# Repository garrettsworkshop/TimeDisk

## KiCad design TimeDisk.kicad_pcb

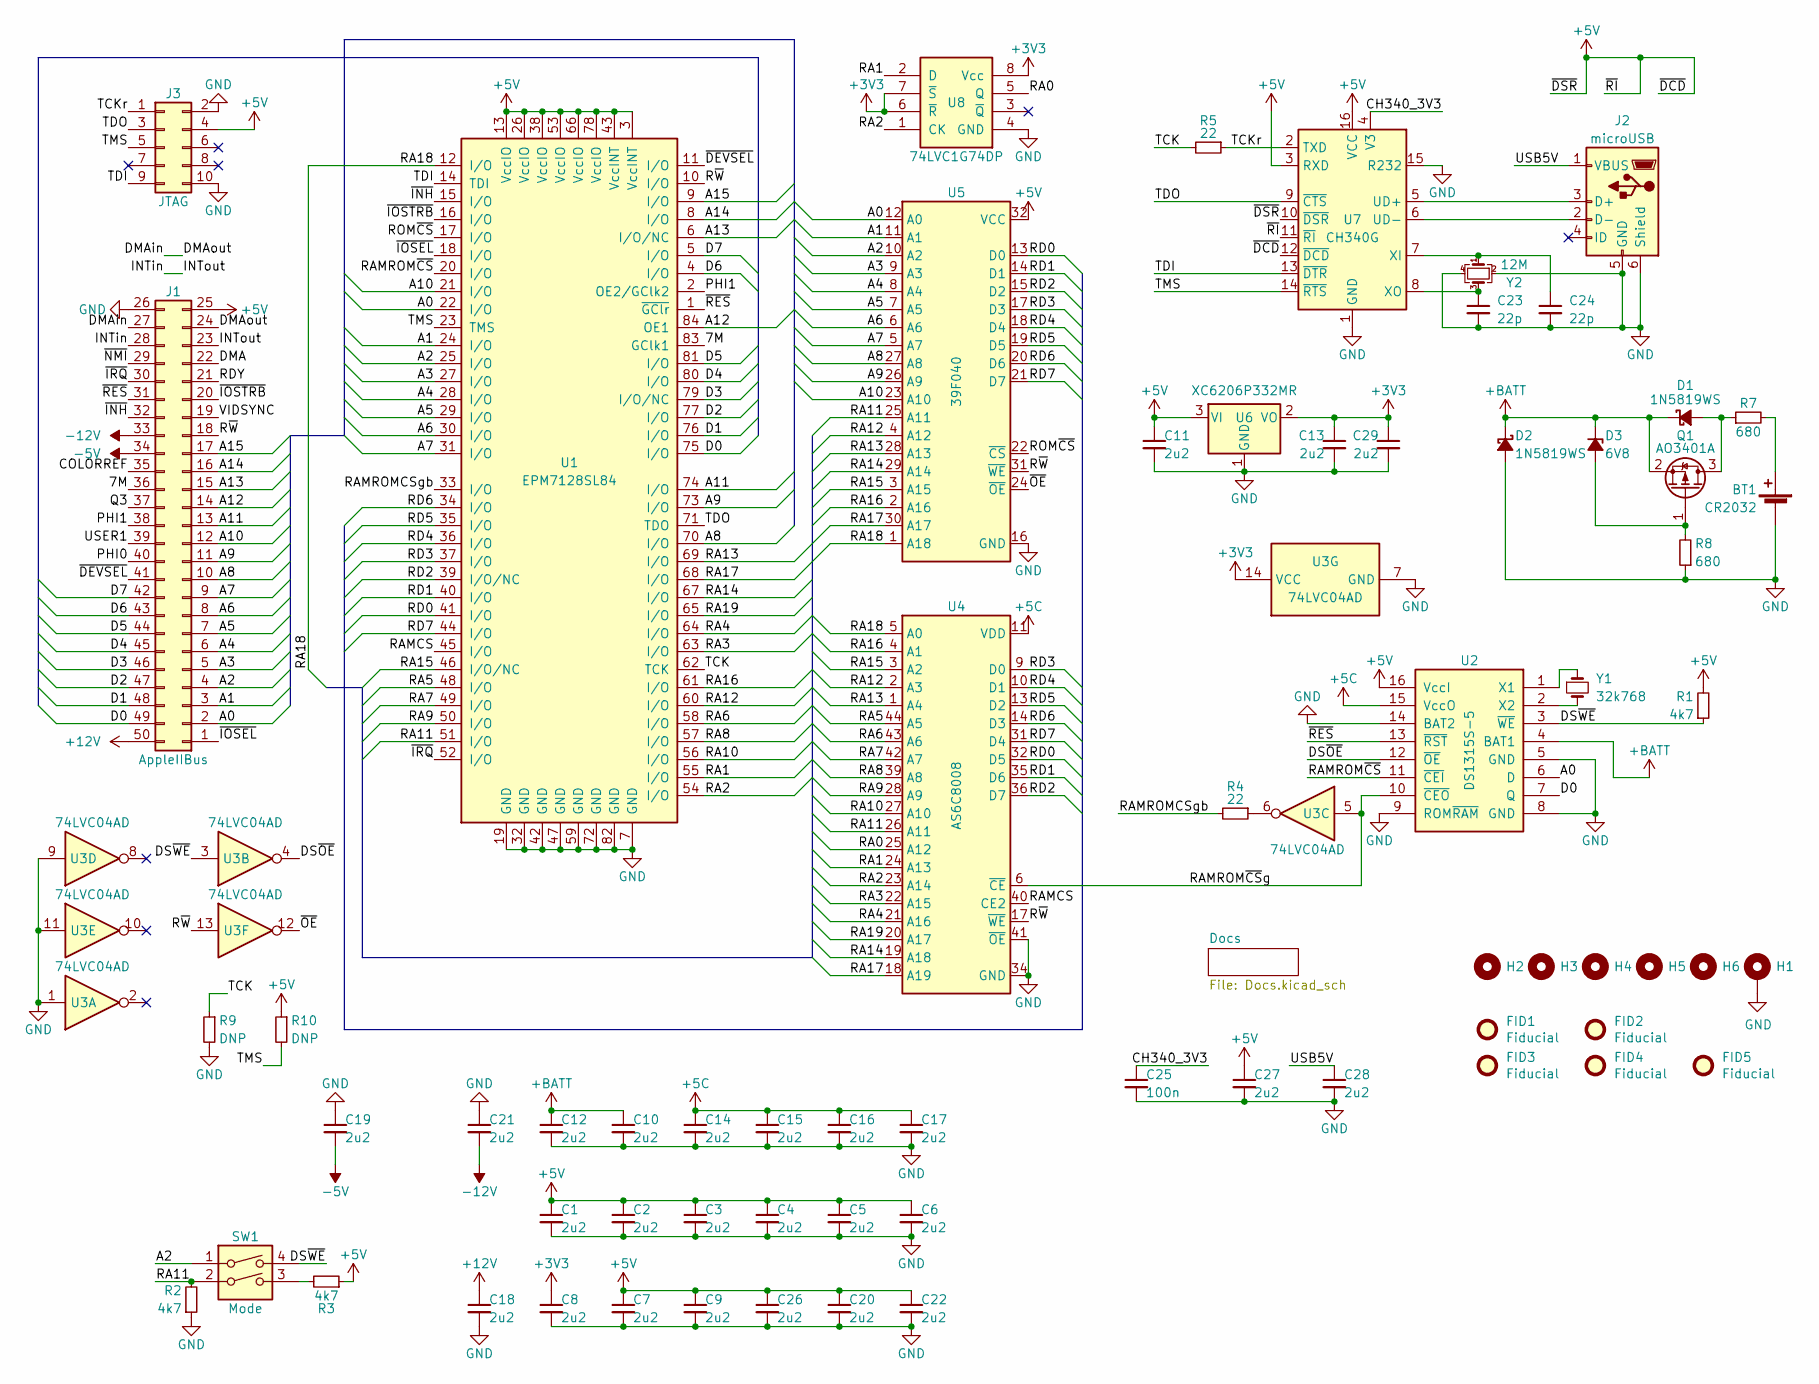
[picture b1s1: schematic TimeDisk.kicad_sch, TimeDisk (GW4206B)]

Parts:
BT1: CR2032; Keystone_3034_2032; LCSC Part C964833
C1, C2, C3, C4, C5, C6, C7, C8, C9, C10, C11, C12, C13, C14, C15, C16, C17, C18, C19, C20, C21, C22, C26, C27, C28, C29: 2u2; C_0805; LCSC Part C87994
C23, C24: 22p; C_0603; LCSC Part C1653
C25: 100n; C_0603; LCSC Part C28233
D1, D2: 1N5819WS; D_SOD-123; LCSC Part C191023
D3: 6V8; D_SOD-323; LCSC Part C118604
FID1, FID2, FID3, FID4, FID5: Fiducial
H1: PasteHole_1.1mm_PTH
H2, H3, H4, H5, H6: PasteHole_1.152mm_NPTH
J1: AppleIIBus; AppleIIBus_Edge
J2: microUSB; USB_Micro-B_Amphenol_10118192-0001; LCSC Part C132564
J3: JTAG; Header_2x5_Unshrouded_P1.27mm
Q1: AO3401A; SOT-23; LCSC Part C15127
R1, R2, R3: 4k7; R_0805; LCSC Part C17673
R4, R5: 22; R_0805; LCSC Part C17561
R7, R8: 680; R_0805; LCSC Part C17798
R9, R10: DNP; R_0805
SW1: Mode; SW_DIP_SPSTx02_Slide_DSHP02TS_P1.27mm
U1: EPM7128SL84; PLCC-84
U2: DS1315S-5; SOIC-16_7.5mm
U3: 74LVC04AD; SOIC-14_3.9mm; LCSC Part C190764
U4: AS6C8008; TSOP-II-44_400mil_P0.8mm; LCSC Part C1349342
U5: 39F040; PLCC-32_SMDSocket; LCSC Part C645936
U6: XC6206P332MR; SOT-23; LCSC Part C5446
U7: CH340G; SOIC-16_3.9mm; LCSC Part C14267
U8: 74LVC1G74DP; NXP_TSSOP-8_3x3mm_P0.65mm; LCSC Part C458768
Y1: 32k768; Crystal_C26-LF_D2.1mm_L6.5mm_Horizontal
Y2: 12M; Crystal_SMD_3225-4Pin_3.2x2.5mm; LCSC Part C9002

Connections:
+3V3: C8.1, C13.1, C29.1, U3.14 (VCC), U6.2 (VO), U8.6 (~R), U8.7 (~S), U8.8 (Vcc)
+5C: C14.1, C15.1, C16.1, C17.1, U2.15 (VccO), U4.11 (VDD), U4.33 (VDD)
+5V: C1.1, C2.1, C3.1, C4.1, C5.1, C6.1, C7.1, C9.1, C11.1, C20.1, C22.1, C26.1, C27.1, J1.25, J3.4, R1.2, R3.1, R10.1, U1.3 (VccINT), U1.13 (VccIO), U1.26 (VccIO), U1.38 (VccIO), U1.43 (VccINT), U1.53 (VccIO), U1.66 (VccIO), U1.78 (VccIO), U2.16 (VccI), U5.32 (VCC), U6.3 (VI), U7.3 (RXD), U7.10 (~DSR), U7.11 (~RI), U7.12 (~DCD), U7.16 (VCC)
+12V: C18.1, J1.50
+BATT: C10.1, C12.1, D1.1 (K), D2.1 (K), D3.1 (K), Q1.2 (S), U2.4 (BAT1)
-5V: C19.2, J1.34
-12V: C21.2, J1.33
/7M: J1.36, U1.83 (GClk1)
/A0: J1.2, U1.22 (I/O), U2.6 (D), U5.12 (A0)
/A1: J1.3, U1.24 (I/O), U5.11 (A1)
/A2: J1.4, SW1.1, U1.25 (I/O), U5.10 (A2)
/A3: J1.5, U1.27 (I/O), U5.9 (A3)
/A4: J1.6, U1.28 (I/O), U5.8 (A4)
/A5: J1.7, U1.29 (I/O), U5.7 (A5)
/A6: J1.8, U1.30 (I/O), U5.6 (A6)
/A7: J1.9, U1.31 (I/O), U5.5 (A7)
/A8: J1.10, U1.70 (I/O), U5.27 (A8)
/A9: J1.11, U1.73 (I/O), U5.26 (A9)
/A10: J1.12, U1.21 (I/O), U5.23 (A10)
/A11: J1.13, U1.74 (I/O)
/A12: J1.14, U1.84 (OE1)
/A13: J1.15, U1.6 (I/O/NC)
/A14: J1.16, U1.8 (I/O)
/A15: J1.17, U1.9 (I/O)
/CH340_3V3: C25.1, U7.4 (V3)
/COLORREF: J1.35
/D0: J1.49, U1.75 (I/O), U2.7 (Q)
/D1: J1.48, U1.76 (I/O)
/D2: J1.47, U1.77 (I/O)
/D3: J1.46, U1.79 (I/O/NC)
/D4: J1.45, U1.80 (I/O)
/D5: J1.44, U1.81 (I/O)
/D6: J1.43, U1.4 (I/O)
/D7: J1.42, U1.5 (I/O)
/DMA: J1.22
/DMAin: J1.24, J1.27
/DS~OE: U2.12 (~OE), U3.4
/DS~WE: R1.1, SW1.4, U2.3 (~WE), U3.3
/INTin: J1.23, J1.28
/PHI0: J1.40
/PHI1: J1.38, U1.2 (OE2/GClk2)
/Q3: J1.37
/RA0: U4.25 (A12), U8.5 (Q)
/RA1: U1.55 (I/O), U4.24 (A13), U8.2 (D)
/RA2: U1.54 (I/O), U4.23 (A14), U8.1 (CK)
/RA3: U1.63 (I/O), U4.22 (A15)
/RA4: U1.64 (I/O), U4.21 (A16)
/RA5: U1.48 (I/O), U4.44 (A5)
/RA6: U1.58 (I/O), U4.43 (A6)
/RA7: U1.49 (I/O), U4.42 (A7)
/RA8: U1.57 (I/O), U4.39 (A8)
/RA9: U1.50 (I/O), U4.28 (A9)
/RA10: U1.56 (I/O), U4.27 (A10)
/RA11: R2.2, SW1.2, U1.51 (I/O), U4.26 (A11), U5.25 (A11)
/RA12: U1.60 (I/O), U4.2 (A3), U5.4 (A12)
/RA13: U1.69 (I/O), U4.1 (A4), U5.28 (A13)
/RA14: U1.67 (I/O), U4.19 (A18), U5.29 (A14)
/RA15: U1.46 (I/O/NC), U4.3 (A2), U5.3 (A15)
/RA16: U1.61 (I/O), U4.4 (A1), U5.2 (A16)
/RA17: U1.68 (I/O), U4.18 (A19), U5.30 (A17)
/RA18: U1.12 (I/O), U4.5 (A0), U5.1 (A18)
/RA19: U1.65 (I/O), U4.20 (A17)
/RAMCS: U1.45 (I/O), U4.40 (CE2)
/RAMROMCSgb: R4.2, U1.33 (I/O)
/RAMROM~CS: U1.20 (I/O), U2.11 (~CEI)
/RAMROM~CSg: U2.10 (~CEO), U3.5, U4.6 (~CE)
/RD0: U1.41 (I/O), U4.32 (D5), U5.13 (D0)
/RD1: U1.40 (I/O), U4.35 (D6), U5.14 (D1)
/RD2: U1.39 (I/O/NC), U4.36 (D7), U5.15 (D2)
/RD3: U1.37 (I/O), U4.9 (D0), U5.17 (D3)
/RD4: U1.36 (I/O), U4.10 (D1), U5.18 (D4)
/RD5: U1.35 (I/O), U4.13 (D2), U5.19 (D5)
/RD6: U1.34 (I/O), U4.14 (D3), U5.20 (D6)
/RD7: U1.44 (I/O), U4.31 (D4), U5.21 (D7)
/RDY: J1.21
/ROM~CS: U1.17 (I/O), U5.22 (~CS)
/R~W: J1.18, U1.10 (I/O), U3.13, U4.17 (~WE), U5.31 (~WE)
/TCK: R5.2, R9.1, U1.62 (TCK)
/TCKr: J3.1, R5.1, U7.2 (TXD)
/TDI: J3.9, U1.14 (TDI), U7.13 (~DTR)
/TDO: J3.3, U1.71 (TDO), U7.9 (~CTS)
/TMS: J3.5, R10.2, U1.23 (TMS), U7.14 (~RTS)
/USB5V: C28.1, J2.1 (VBUS)
/USER1: J1.39
/VIDSYNC: J1.19
/~DEVSEL: J1.41, U1.11 (I/O)
/~INH: J1.32, U1.15 (I/O)
/~IOSEL: J1.1, U1.18 (I/O)
/~IOSTRB: J1.20, U1.16 (I/O)
/~IRQ: J1.30, U1.52 (I/O)
/~NMI: J1.29
/~OE: U3.12, U5.24 (~OE)
/~RES: J1.31, U1.1 (~GClr), U2.13 (~RST)
GND: BT1.2 (-), C1.2, C2.2, C3.2, C4.2, C5.2, C6.2, C7.2, C8.2, C9.2, C10.2, C11.2, C12.2, C13.2, C14.2, C15.2, C16.2, C17.2, C18.2, C19.1, C20.2, C21.1, C22.2, C23.2, C24.2, C25.2, C26.2, C27.2, C28.2, C29.2, D2.2 (A), H1.1, J1.26, J2.5 (GND), J2.6 (Shield), J3.2, J3.10, R2.1, R8.1, R9.2, U1.7 (GND), U1.19 (GND), U1.32 (GND), U1.42 (GND), U1.47 (GND), U1.59 (GND), U1.72 (GND), U1.82 (GND), U2.5 (GND), U2.8 (GND), U2.9 (ROM~RAM), U2.14 (BAT2), U3.1, U3.7 (GND), U3.9, U3.11, U4.12 (GND), U4.34 (GND), U4.41 (~OE), U5.16 (GND), U6.1 (GND), U7.1 (GND), U7.15 (R232), U8.4 (GND), Y2.2, Y2.4
unnamed: BT1.1 (+), R7.2
unnamed: D1.2 (A), Q1.3 (D), R7.1
unnamed: D3.2 (A), Q1.1 (G), R8.2
unnamed: J2.3 (D+), U7.5 (UD+)
unnamed: J2.2 (D-), U7.6 (UD-)
unnamed: R3.2, SW1.3
unnamed: R4.1, U3.6
unnamed: U2.1 (X1), Y1.1
unnamed: U2.2 (X2), Y1.2
unnamed: C24.1, U7.7 (XI), Y2.1
unnamed: C23.1, U7.8 (XO), Y2.3

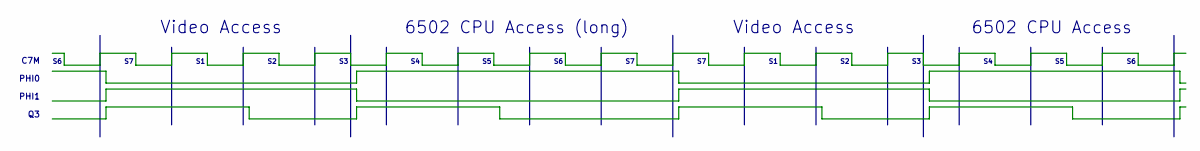
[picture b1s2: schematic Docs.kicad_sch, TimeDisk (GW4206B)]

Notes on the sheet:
PHI0
6502 CPU Access (long)
Video Access
6502 CPU Access
PHI1
C7M

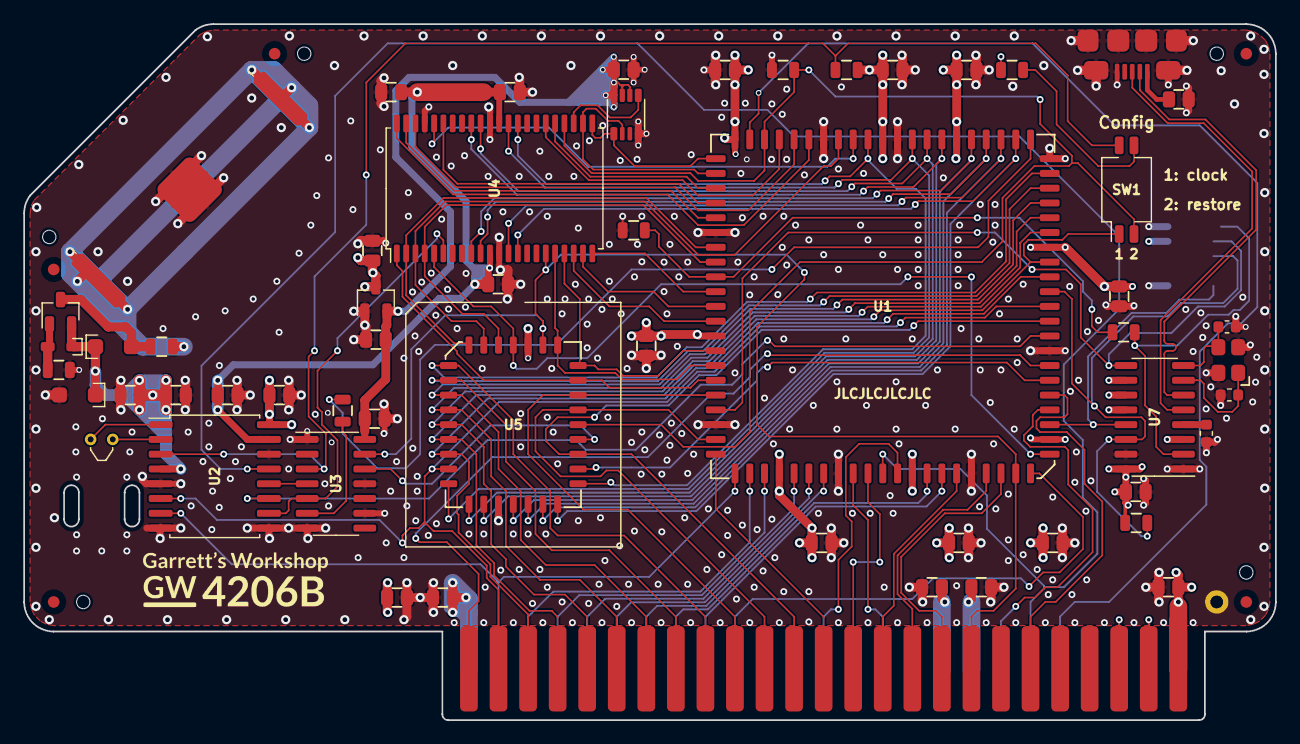
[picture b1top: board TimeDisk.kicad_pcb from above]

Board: 4 copper layers, 107.6 x 59.8 mm, 68 parts (1 on the bottom side), 97 nets.

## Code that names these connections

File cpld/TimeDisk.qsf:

# -------------------------------------------------------------------------- #
#
# Copyright (C) 1991-2013 Altera Corporation
# Your use of Altera Corporation's design tools, logic functions 
# and other software and tools, and its AMPP partner logic 
# functions, and any output files from any of the foregoing 
# (including device programming or simulation files), and any 
# associated documentation or information are expressly subject 
# to the terms and conditions of the Altera Program License 
# Subscription Agreement, Altera MegaCore Function License 
# Agreement, or other applicable license agreement, including, 
# without limitation, that your use is for the sole purpose of 
# programming logic devices manufactured by Altera and sold by 
# Altera or its authorized distributors.  Please refer to the 
# applicable agreement for further details.
#
# -------------------------------------------------------------------------- #
#
# Quartus II 64-Bit
# Version 13.0.1 Build 232 06/12/2013 Service Pack 1 SJ Web Edition
# Date created = 23:54:33  February 19, 2023
#
# -------------------------------------------------------------------------- #
#
# Notes:
#
# 1) The default values for assignments are stored in the file:
#		TimeDisk_assignment_defaults.qdf
#    If this file doesn't exist, see file:
#		assignment_defaults.qdf
#
# 2) Altera recommends that you do not modify this file. This
#    file is updated automatically by the Quartus II software
#    and any changes you make may be lost or overwritten.
#
# -------------------------------------------------------------------------- #


set_global_assignment -name FAMILY MAX7000S
set_global_assignment -name DEVICE "EPM7128SLC84-15"
set_global_assignment -name TOP_LEVEL_ENTITY TimeDisk
set_global_assignment -name ORIGINAL_QUARTUS_VERSION "13.0 SP1"
set_global_assignment -name PROJECT_CREATION_TIME_DATE "23:54:33  FEBRUARY 19, 2023"
set_global_assignment -name LAST_QUARTUS_VERSION "13.0 SP1"
set_global_assignment -name PROJECT_OUTPUT_DIRECTORY output_files
set_global_assignment -name ERROR_CHECK_FREQUENCY_DIVISOR "-1"
set_global_assignment -name MIN_CORE_JUNCTION_TEMP 0
set_global_assignment -name MAX_CORE_JUNCTION_TEMP 85
set_global_assignment -name VERILOG_FILE TimeDisk.v
set_location_assignment PIN_1 -to nRES
set_location_assignment PIN_52 -to nIRQ
set_location_assignment PIN_6 -to A[13]
set_location_assignment PIN_4 -to D[6]
set_location_assignment PIN_5 -to D[7]
set_location_assignment PIN_84 -to A[12]
set_location_assignment PIN_8 -to A[14]
set_location_assignment PIN_9 -to A[15]
set_location_assignment PIN_10 -to nWE
set_location_assignment PIN_11 -to nDEVSEL
set_location_assignment PIN_18 -to nIOSEL
set_location_assignment PIN_16 -to nIOSTRB
set_location_assignment PIN_17 -to nROMCS
set_location_assignment PIN_20 -to nRAMROMCS
set_location_assignment PIN_21 -to A[10]
set_location_assignment PIN_22 -to A[0]
set_location_assignment PIN_24 -to A[1]
set_location_assignment PIN_25 -to A[2]
set_location_assignment PIN_27 -to A[3]
set_location_assignment PIN_28 -to A[4]
set_location_assignment PIN_29 -to A[5]
set_location_assignment PIN_30 -to A[6]
set_location_assignment PIN_31 -to A[7]
set_location_assignment PIN_33 -to RAMROMCSgb
set_location_assignment PIN_34 -to RD[6]
set_location_assignment PIN_35 -to RD[5]
set_location_assignment PIN_36 -to RD[4]
set_location_assignment PIN_37 -to RD[3]
set_location_assignment PIN_39 -to RD[2]
set_location_assignment PIN_40 -to RD[1]
set_location_assignment PIN_44 -to RD[7]
set_location_assignment PIN_45 -to RAMCS
set_location_assignment PIN_46 -to RAH[15]
set_location_assignment PIN_51 -to RA11
set_location_assignment PIN_41 -to RD[0]
set_location_assignment PIN_61 -to RAH[16]
set_location_assignment PIN_60 -to RAH[12]
set_location_assignment PIN_67 -to RAH[14]
set_location_assignment PIN_68 -to RAH[17]
set_location_assignment PIN_69 -to RAH[13]
set_location_assignment PIN_70 -to A[8]
set_location_assignment PIN_73 -to A[9]
set_location_assignment PIN_74 -to A[11]
set_location_assignment PIN_75 -to D[0]
set_location_assignment PIN_76 -to D[1]
set_location_assignment PIN_77 -to D[2]
set_location_assignment PIN_79 -to D[3]
set_location_assignment PIN_80 -to D[4]
set_location_assignment PIN_81 -to D[5]
set_location_assignment PIN_83 -to C7M
set_location_assignment PIN_15 -to nINH
set_location_assignment PIN_12 -to RAH[18]
set_location_assignment PIN_48 -to RAL[5]
set_location_assignment PIN_49 -to RAL[7]
set_location_assignment PIN_50 -to RAL[9]
set_location_assignment PIN_54 -to RAL[1]
set_location_assignment PIN_55 -to RAL[2]
set_location_assignment PIN_56 -to RAL[10]
set_location_assignment PIN_57 -to RAL[8]
set_location_assignment PIN_58 -to RAL[6]
set_location_assignment PIN_63 -to RAL[3]
set_location_assignment PIN_64 -to RAL[4]
set_location_assignment PIN_65 -to RAH[19]
set_location_assignment PIN_2 -to PHI1
set_instance_assignment -name MAX7000_INDIVIDUAL_TURBO_BIT ON -to CSDBEN
set_global_assignment -name SYNTH_TIMING_DRIVEN_SYNTHESIS OFF
set_global_assignment -name MAX7000_IGNORE_LCELL_BUFFERS OFF
set_global_assignment -name OPTIMIZE_HOLD_TIMING OFF
set_global_assignment -name OPTIMIZE_MULTI_CORNER_TIMING OFF
set_global_assignment -name FITTER_EFFORT "STANDARD FIT"
set_global_assignment -name SLOW_SLEW_RATE ON
set_global_assignment -name AUTO_TURBO_BIT OFF
set_instance_assignment -name MAX7000_INDIVIDUAL_TURBO_BIT ON -to nROMCS_MC
set_instance_assignment -name MAX7000_INDIVIDUAL_TURBO_BIT ON -to nRAMROMCS_MC
set_instance_assignment -name MAX7000_INDIVIDUAL_TURBO_BIT ON -to RAMCS_MC
set_instance_assignment -name MAX7000_INDIVIDUAL_TURBO_BIT ON -to DOE
set_instance_assignment -name MAX7000_INDIVIDUAL_TURBO_BIT ON -to RAMSEL_MC
set_global_assignment -name MAX7000_DEVICE_IO_STANDARD TTL

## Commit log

2019-07-24 Done but I should probably buffer the data bus
2019-07-26 Buffered data bus with CPLD
2019-07-30 Changed ROM OE strategy
    Has gerbers submitted to JLCPCB though
2019-07-30 Finished layout with new OE stuff.
    Updated gerbers and zip
2019-07-30 Submitted to JLCPCB
2019-08-20 Can't fit...
2019-08-25 Lots of state machine work
2019-09-05 Merged changes from GR8RAM, e.g. pipelined add
2019-09-06 Trying this on reworked boards
2019-09-06 Compiles, 512k ram
2019-09-06 Clarified assignments
2019-09-07 Corrected comment in TimeMachine.v
2019-09-08 Changed organization of CPLD source file
2019-10-01 Fixed mistake, submitted to JLCPCB
2019-10-02 CPLD firmware for revised TimeMachine
2019-10-11 Switched schematic to new GW libraries
2019-10-12 1 MB verilog for fixed board
2019-10-13 Changed libraries
2019-10-14 TimeMachine prototype CPLD design works on IIgs
2019-10-18 New PLD revision
    For write operations, register data is latched in the middle of S6, 70ns before the end of PHI0. This gives more write data setup time, which may be needed on the Apple II with the 1 MHz 6502.
2019-12-21 Removed state counter reset
2020-01-26 Separated CSDBEN
2020-02-09 Removed AVR-JTAG-10 connector footprint
2020-02-09 Removed sch-bak and rescue files
2020-02-17 Combined WRCSEN and RDCSEN
2020-02-18 Fixed IOROMEN wrong enablement
2020-02-26 Removed SetWR and FullIOIOEN
2020-02-26 Extended address to 24 bits
2020-02-26 Removed inhibit output from CPLD
2020-02-26 Moved REGEN and IOROMEN (no functional change)
2020-02-26 Added configuration section
2020-02-26 Added transfer counters
2020-02-26 Load mode after reset
2020-02-26 Put FullIOEN back
2020-03-10 many PLD changes to do new pseudo-DMA stuff
2021-04-12 Revert "many PLD changes to do new pseudo-DMA stuff"
    This reverts commit 37f770932066a3aa4669307f4ca01c1315b127dd.
2021-04-12 Revert "Put FullIOEN back"
    This reverts commit 5a0f81433fe23d6546322834e2fff1281688e5e1.
2021-04-12 Revert "Load mode after reset"
    This reverts commit ecc4bd388a559ac0a6b28390bb74bd62fba98773.
2021-04-12 Revert "Added transfer counters"
    This reverts commit 2964d55a3a07f81c50b8d563ba349579e8b3907a.
2021-04-12 Revert "Added configuration section"
    This reverts commit d9ef300597d9ec0d7768a5c8f5e0210d565998a8.
2021-04-12 Compiled
2021-04-12 Regenerated gerbers
2021-04-12 Simplified ROM layout
2021-04-12 Updated driver ROMs
2021-04-17 Fix RamFactor-1.4.bin
2021-05-22 did i fix it here?
2022-09-17 Add SVF files
2022-12-09 Newer
2023-02-20 More robust reset and PHI1 synchronization handling
2023-02-20 New "TimeDisk" Quartus project
2023-02-20 Add mode jumper
2023-02-28 TimeDisk rev.A
2023-02-28 Remove CPLD and driver stuff... use rev. B
2023-02-28 Compile TimeDisk and create SVF file
2023-03-23 Passes self-test but removed mode/extended bank functionality
2023-03-23 works
2023-03-23 Added bank back
2023-03-23 compiled lol
2023-03-30 Final GW4206A revision
2023-03-30 Remove old svf files
2023-06-07 Add timer
2023-09-23 Add back rev. A CPLD stuff
2023-09-24 Syntax changes but same fusemap
2023-09-25 fixed SVF
2023-09-28 Fixed /IOSEL hold time after C7M issue on IIgs
2024-01-27 idk if it's even good
2024-02-15 Create Makefile
2024-02-15 Done?
2024-02-16 As sent to JLC
2024-02-29 Start C revision
2024-03-06 Start on hibernate
2024-03-11 Add RPP
2024-03-18 Update via-to-via clearance rules and update footprints
2024-03-22 with hole
2024-03-29 RC 1.1
2024-03-29 Go back to calling this version 1.0... RC 1.0
2024-05-14 B.1.0 RC2/3
